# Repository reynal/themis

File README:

Themis is a hybrid analog-digital music synthetizer that leverages both analog and digital hardware to generate the richest synthetizer sound ever.

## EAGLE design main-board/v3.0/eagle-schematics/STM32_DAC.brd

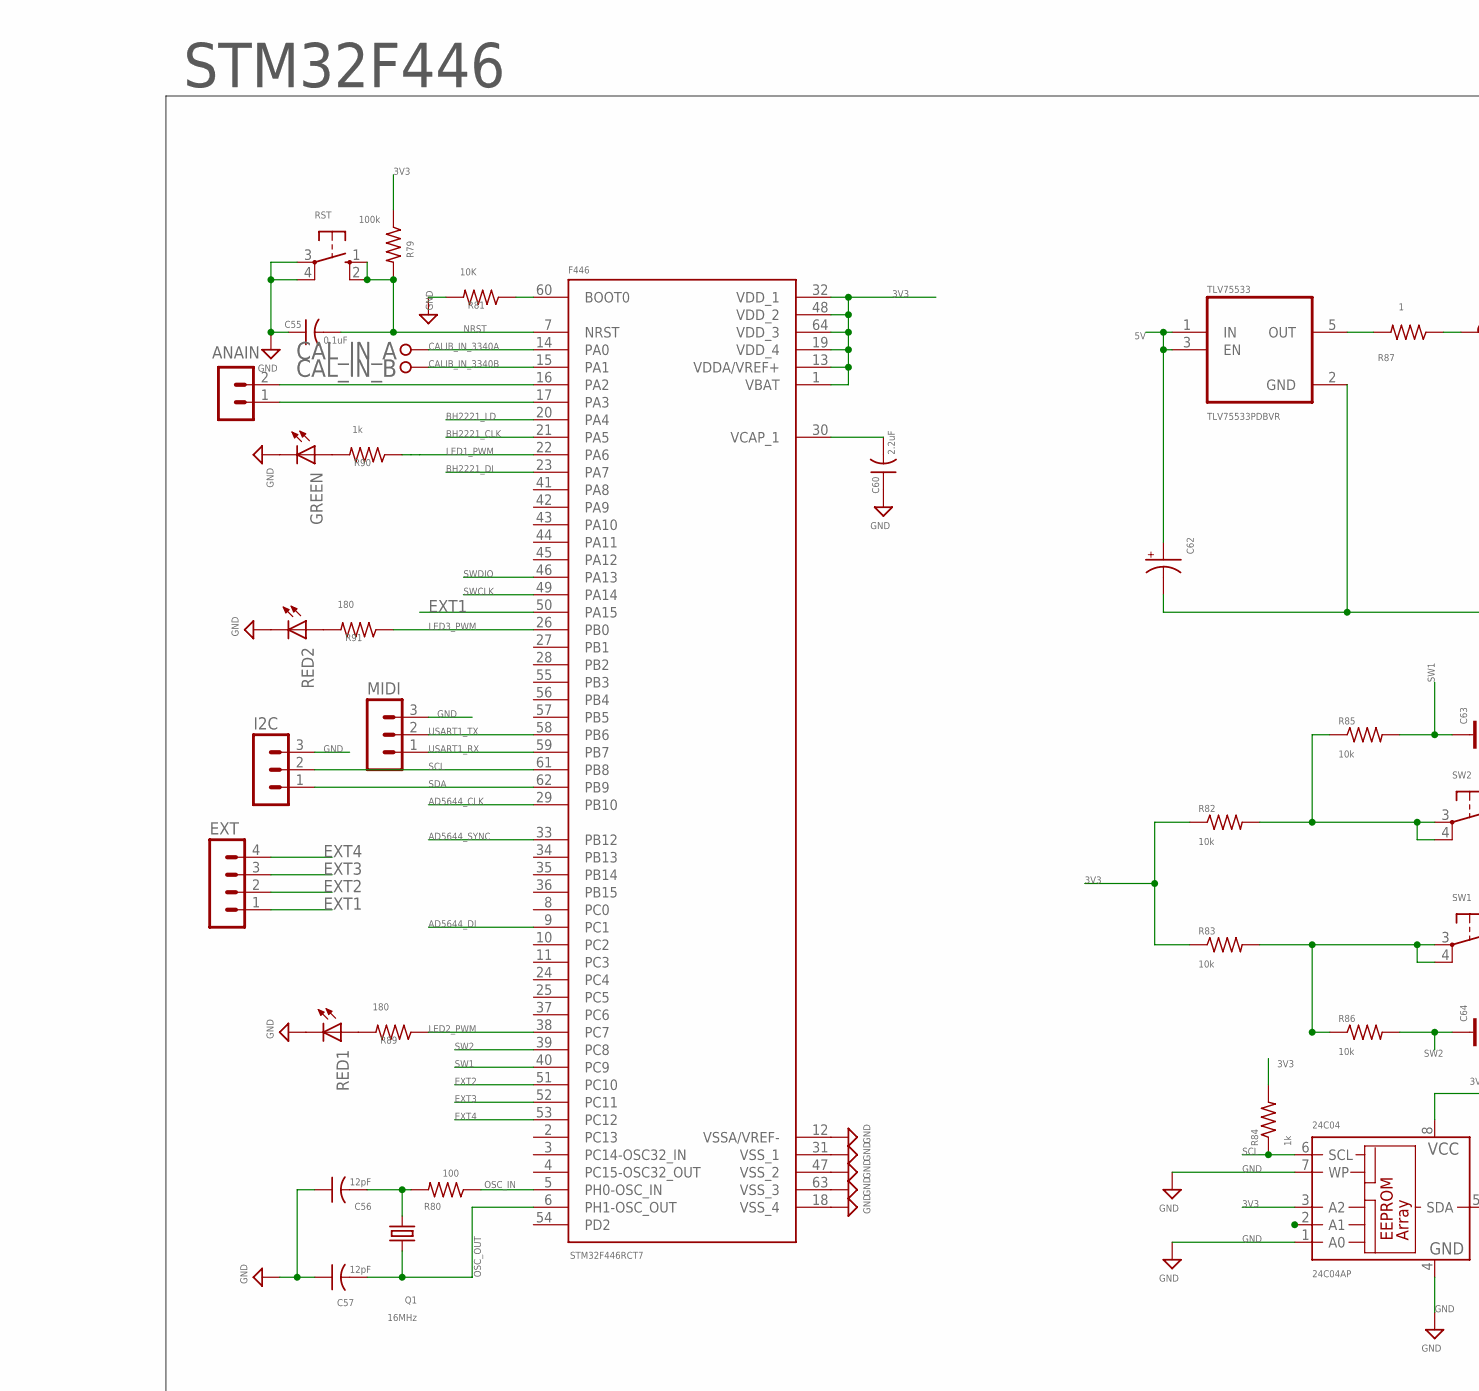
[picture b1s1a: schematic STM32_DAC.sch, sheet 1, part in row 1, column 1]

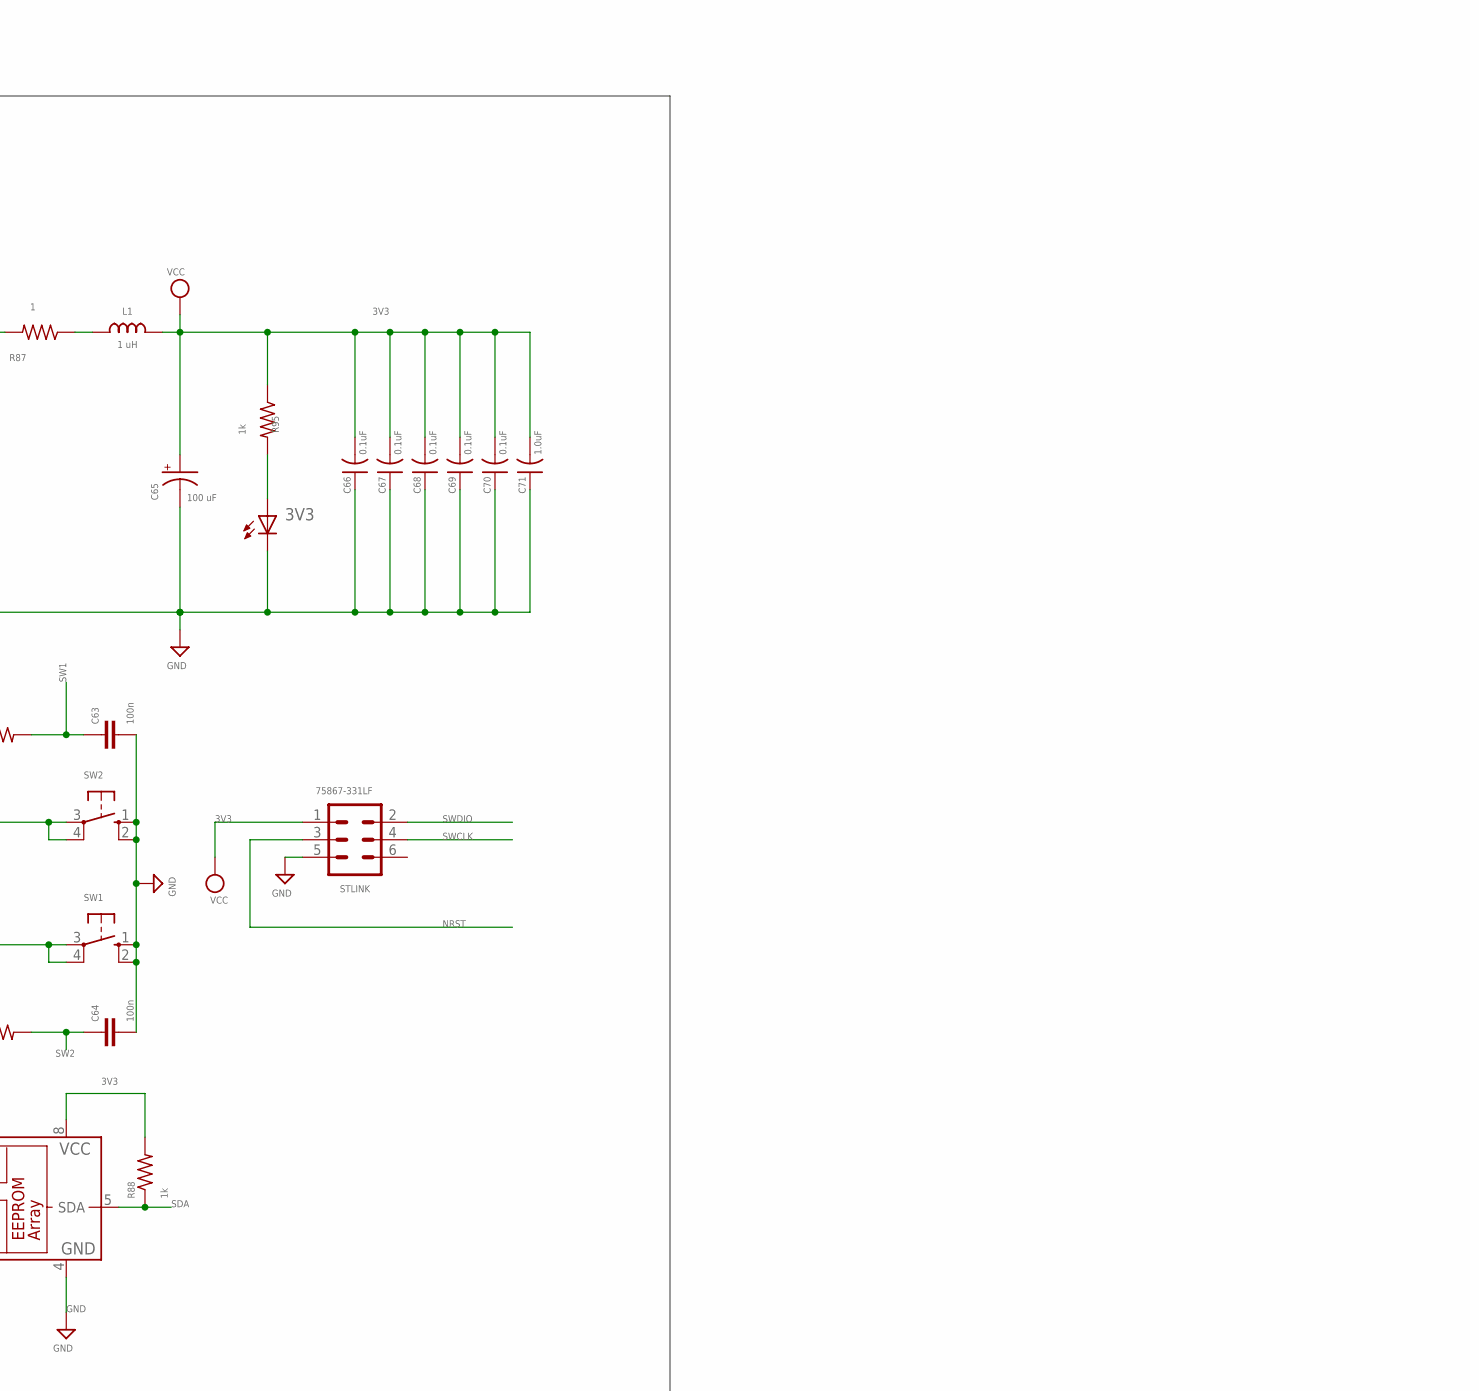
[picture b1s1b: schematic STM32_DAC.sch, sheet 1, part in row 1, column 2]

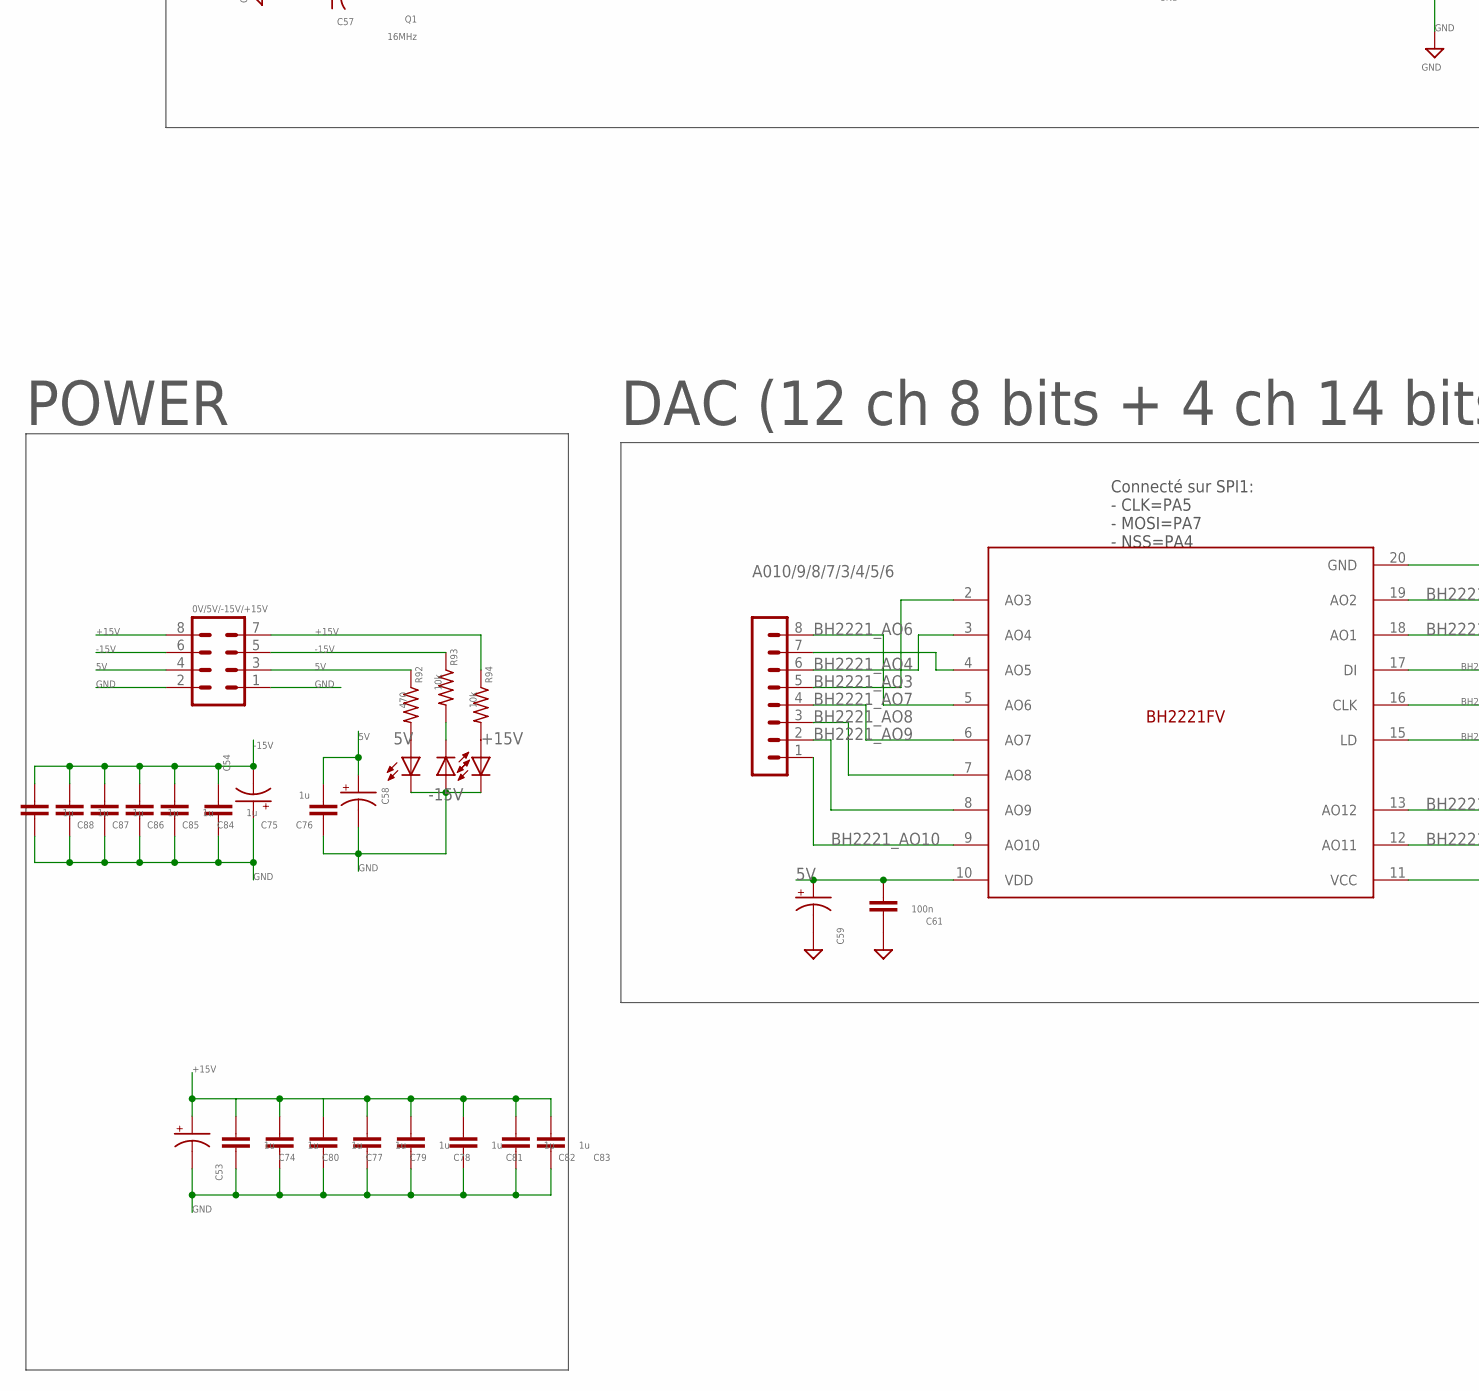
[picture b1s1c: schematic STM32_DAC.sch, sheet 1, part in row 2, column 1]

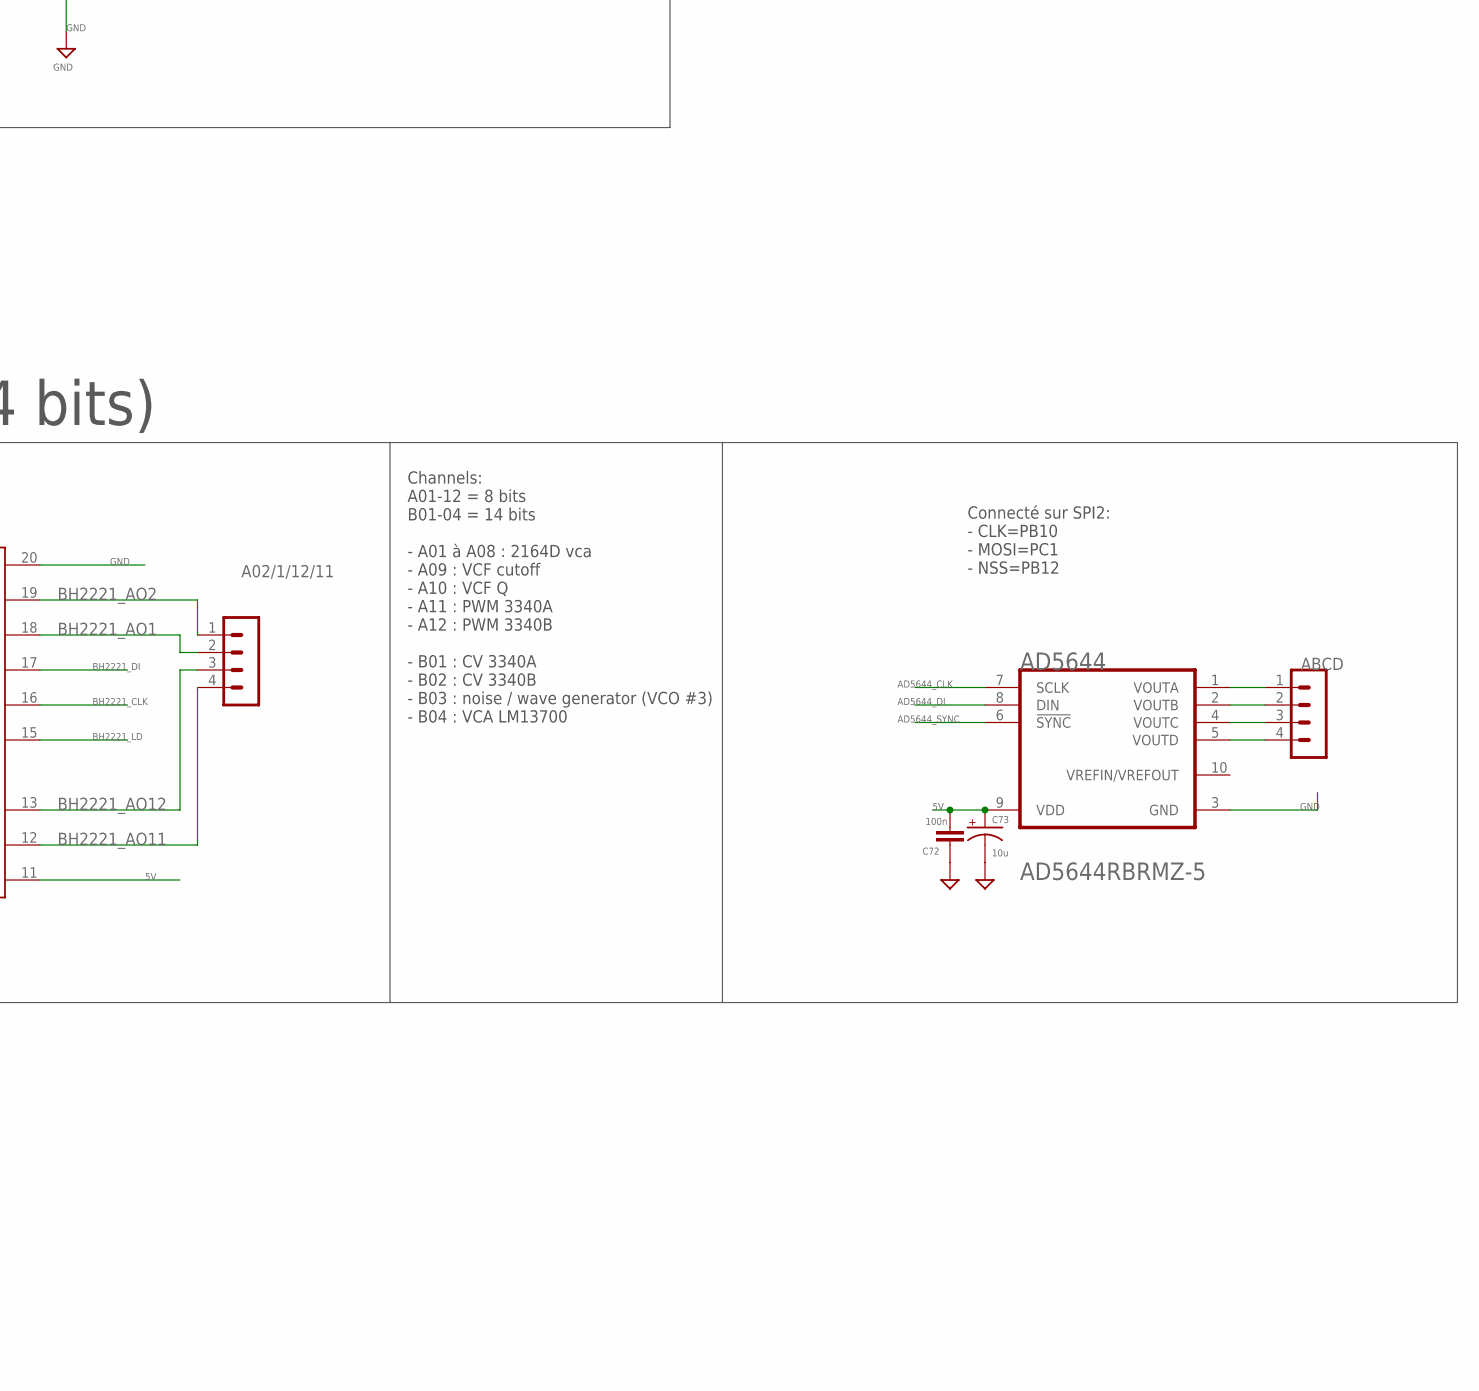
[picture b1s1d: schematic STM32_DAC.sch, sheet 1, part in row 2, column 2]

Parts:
0V/5V/-15V/+15V: MA04-2
3V3: LED-0805; 0805-LED
5V: LED-0603; 0603-LED
24C04: 24C04AP; DIL8
+15V: LED-0805; 0805-LED
-15V: LED-0805; 0805-LED
A02/1/12/11: MA04-1
A010/9/8/7/3/4/5/6: MA08-1
ABCD: MA04-1
AD5644: ANALOG_DEVICES_AD5644RBRMZ-5ANALOG_DEVICES_AD5644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; ANALOG_DEVICES_AD5644RBRMZ-5_0
ANAIN: MA02-1
BH2221: BH2221FV; SOP65P780X200-20N
C53, C54, C58, C59, C62, C73: 10u; CPOL2917
C55, C66, C67, C68, C69, C70: 0.1uF; C0805
C56, C57: 12pF; C0805
C60: 2.2uF; C0805
C61, C72: 100n; C1206
C63, C64: 100n; C0805
C65: 100 uF; CPOL2917
C71: 1.0uF; C0805
C74, C75, C76, C77, C78, C79, C80, C81, C82, C83, C84, C85, C86, C87, C88: 1u; C1206
CAL_IN_A: TESTPOINT; TESTPOINT_63
CAL_IN_B: TESTPOINT; TESTPOINT_63
EXT: MA04-1
F446: STM32F446RCT7; QFP50P1200X1200X160-64N
GREEN: LED-0805; 0805-LED
I2C: MA03-1
L1: 1 uH; L0805
MIDI: MA03-1
Q1: 16MHz; Q-HC-46X
R79: 100k; R0805
R80: 100; R0805
R81: 10K; R0805
R82, R83, R85, R86, R93, R94: 10k; R0805
R84, R88, R90, R95: 1k; R0805
R87: 1; R0805
R89, R91: 180; R0805
R92: 470; R0805
RED1, RED2: LED-0603; 0603-LED
RST: 10-XX; B3F-10XX
STLINK: 75867-331LF; MA03-2
SW1, SW2: 10-XX; B3F-10XX
TLV75533: TLV75533PDBVR; SOT95P280X145-5N

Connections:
3V3: 24C04.2 (A1), 24C04.3 (A2), 24C04.8 (VCC), C65.+, C66.2, C67.2, C68.2, C69.2, C70.2, C71.2, F446.1 (VBAT), F446.13 (VDDA/VREF+), F446.19 (VDD_4), F446.32 (VDD_1), F446.48 (VDD_2), F446.64 (VDD_3), L1.2, R79.1, R82.1, R83.1, R84.2, R88.2, R95.1, STLINK.1
5V: 0V/5V/-15V/+15V.3, 0V/5V/-15V/+15V.4, AD5644.9 (VDD), BH2221.10 (VDD), BH2221.11 (VCC), C58.+, C59.+, C61.2, C62.+, C72.2, C73.+, C76.2, R92.1, TLV75533.1 (IN), TLV75533.3 (EN)
+15V: 0V/5V/-15V/+15V.7, 0V/5V/-15V/+15V.8, C53.+, C74.2, C77.2, C78.2, C79.2, C80.2, C81.2, C82.2, C83.2, R94.1
-15V: 0V/5V/-15V/+15V.5, 0V/5V/-15V/+15V.6, C54.-, C75.2, C84.2, C85.2, C86.2, C87.2, C88.2, R93.1
AD5644_CLK: AD5644.7 (SCLK), F446.29 (PB10)
AD5644_DI: AD5644.8 (DIN), F446.9 (PC1)
AD5644_SYNC: AD5644.6 (!SYNC!), F446.33 (PB12)
BH2221_AO1: A02/1/12/11.2, BH2221.18 (AO1)
BH2221_AO2: A02/1/12/11.1, BH2221.19 (AO2)
BH2221_AO3: A010/9/8/7/3/4/5/6.5, BH2221.2 (AO3)
BH2221_AO4: A010/9/8/7/3/4/5/6.6, BH2221.3 (AO4)
BH2221_AO6: A010/9/8/7/3/4/5/6.8, BH2221.5 (AO6)
BH2221_AO7: A010/9/8/7/3/4/5/6.4, BH2221.6 (AO7)
BH2221_AO8: A010/9/8/7/3/4/5/6.3, BH2221.7 (AO8)
BH2221_AO9: A010/9/8/7/3/4/5/6.2, BH2221.8 (AO9)
BH2221_AO10: A010/9/8/7/3/4/5/6.1, BH2221.9 (AO10)
BH2221_AO11: A02/1/12/11.4, BH2221.12 (AO11)
BH2221_AO12: A02/1/12/11.3, BH2221.13 (AO12)
BH2221_CLK: BH2221.16 (CLK), F446.21 (PA5)
BH2221_DI: BH2221.17 (DI), F446.23 (PA7)
BH2221_LD: BH2221.15 (LD), F446.20 (PA4)
BOOT1: F446.60 (BOOT0), R81.1
CALIB_IN_3340A: CAL_IN_A.P$1, F446.14 (PA0)
CALIB_IN_3340B: CAL_IN_B.P$1, F446.15 (PA1)
EXT1: EXT.1, F446.50 (PA15)
EXT2: EXT.2, F446.51 (PC10)
EXT3: EXT.3, F446.52 (PC11)
EXT4: EXT.4, F446.53 (PC12)
GND: 0V/5V/-15V/+15V.1, 0V/5V/-15V/+15V.2, 3V3.C, 5V.C, 24C04.1 (A0), 24C04.4 (GND), 24C04.7 (WP), +15V.C, -15V.A, AD5644.3 (GND), BH2221.20 (GND), C53.-, C54.+, C55.1, C56.1, C57.1, C58.-, C59.-, C60.1, C61.1, C62.-, C63.2, C64.2, C65.-, C66.1, C67.1, C68.1, C69.1, C70.1, C71.1, C72.1, C73.-, C74.1, C75.1, C76.1, C77.1, C78.1, C79.1, C80.1, C81.1, C82.1, C83.1, C84.1, C85.1, C86.1, C87.1, C88.1, F446.12 (VSSA/VREF-), F446.18 (VSS_4), F446.31 (VSS_1), F446.47 (VSS_2), F446.63 (VSS_3), GREEN.C, I2C.3, MIDI.3, R81.2, RED1.C, RED2.C, RST.3, RST.4 (P1), STLINK.5, SW1.1 (S), SW1.2 (S1), SW2.1 (S), SW2.2 (S1), TLV75533.2 (GND)
LED1_PWM: F446.22 (PA6), R90.1
LED2_PWM: F446.38 (PC7), R89.1
LED3_PWM: F446.26 (PB0), R91.1
unnamed: R82.2, R85.1, SW2.3, SW2.4 (P1)
unnamed: R83.2, R86.1, SW1.3, SW1.4 (P1)
unnamed: A010/9/8/7/3/4/5/6.7, BH2221.4 (AO5)
unnamed: ABCD.1, AD5644.1 (VOUTA)
unnamed: ABCD.2, AD5644.2 (VOUTB)
unnamed: ABCD.3, AD5644.4 (VOUTC)
unnamed: ABCD.4, AD5644.5 (VOUTD)
unnamed: R89.2, RED1.A
unnamed: R91.2, RED2.A
unnamed: 5V.A, R92.2
unnamed: -15V.C, R93.2
unnamed: +15V.A, R94.2
unnamed: GREEN.A, R90.2
unnamed: 3V3.A, R95.2
unnamed: ANAIN.2, F446.16 (PA2)
unnamed: ANAIN.1, F446.17 (PA3)
unnamed: C56.2, Q1.1, R80.2
unnamed: R87.2, TLV75533.5 (OUT)
unnamed: L1.1, R87.1
NRST: C55.2, F446.7 (NRST), R79.2, RST.1 (S), RST.2 (S1), STLINK.3
OSC_IN: F446.5 (PH0-OSC_IN), R80.1
OSC_OUT: C57.2, F446.6 (PH1-OSC_OUT), Q1.2
SCL: 24C04.6 (SCL), F446.61 (PB8), I2C.2, R84.1
SDA: 24C04.5 (SDA), F446.62 (PB9), I2C.1, R88.1
SW1: C63.1, F446.40 (PC9), R85.2
SW2: C64.1, F446.39 (PC8), R86.2
SWCLK: F446.49 (PA14), STLINK.4
SWDIO: F446.46 (PA13), STLINK.2
USART1_RX: F446.59 (PB7), MIDI.1
USART1_TX: F446.58 (PB6), MIDI.2
VCAP1: C60.2, F446.30 (VCAP_1)

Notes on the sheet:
STM32F446
POWER
DAC (12 ch 8 bits + 4 ch 14 bits)
Connecté sur SPI1: - CLK=PA5 - MOSI=PA7 - NSS=PA4
Connecté sur SPI2: - CLK=PB10 - MOSI=PC1 - NSS=PB12
Channels: A01-12 = 8 bits B01-04 = 14 bits - A01 à A08 : 2164D vca - A09 : VCF cutoff - A10 : VCF Q - A11 : PWM 3340A - A12 : PWM 3340B - B01 : CV 3340A - B02 : CV 3340B - B03 : noise / wave generator (VCO #3) - B04 : VCA LM13700

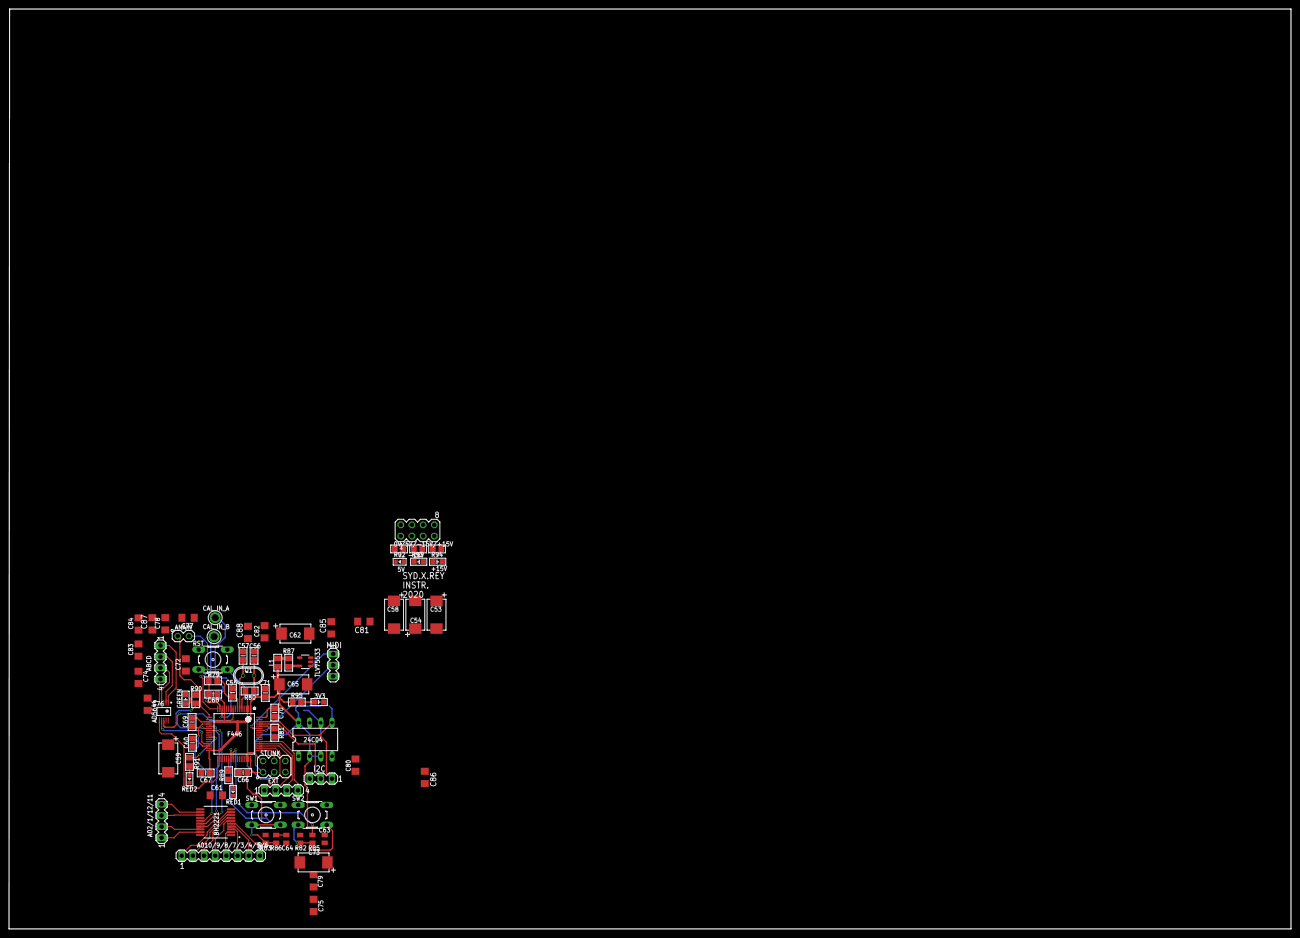
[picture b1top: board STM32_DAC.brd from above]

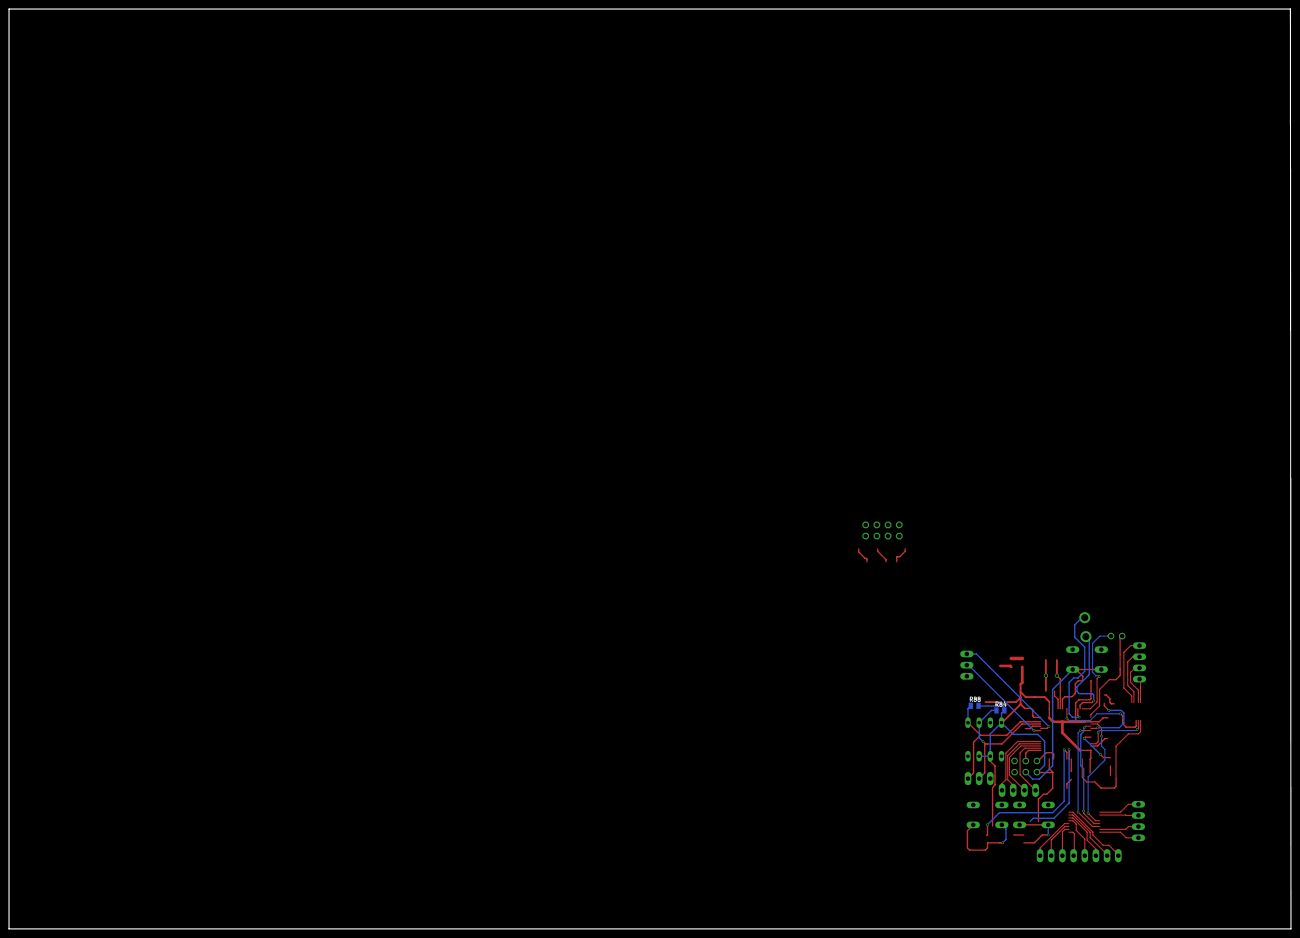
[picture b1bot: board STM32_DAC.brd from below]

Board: 2 copper layers, 291.3 x 209.1 mm, 81 parts (2 on the bottom side), 63 nets.

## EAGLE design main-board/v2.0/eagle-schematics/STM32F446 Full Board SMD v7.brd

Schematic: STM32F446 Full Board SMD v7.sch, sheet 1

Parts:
0V/5V/-15V/+15V: MA04-2
3V3: LED-0805; 0805-LED
5V: LED-0603; 0603-LED
24C04: 24C04AP; DIL8
2164A, 2164B: SSM2164; DIL16
3340A, 3340B: CEM3340; DIL16
+15V: LED-0805; 0805-LED
-15V: LED-0805; 0805-LED
A1, A2, A3, A4: T; TESTPOINT_63
A02/1/12/11: MA04-1
A010/9/8/7/3/4/5/6: MA08-1
ABCD: MA04-1
AD5644: ANALOG_DEVICES_AD5644RBRMZ-5ANALOG_DEVICES_AD5644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; ANALOG_DEVICES_AD5644RBRMZ-5_0
ADG453: ADG453BRZ; SOIC127P600X175-16N
ANAIN: MA02-1
B1, B2, B3, B4: T; TESTPOINT_63
BH2221: BH2221FV; SOP65P780X200-20N
C1, C2, C5, C6, C9, C10, C11, C16, C33, C34, C39, C40, C51, C63, C64: 100n; C0805
C3, C4, C7, C8: 1n; C0805
C12, C13, C14, C15: 10n; C0805
C17, C18, C19, C20, C21, C22, C23, C24, C41: 470n; C0805
C25, C26, C27, C28, C29, C30, C31, C32: 560p; C0805
C35, C46: 100p; C0805
C36, C37, C38: 4.7u; C0805
C42, C44: 1u; C0805
C43, C45, C49, C52: 300p; C0805
C50: 22u; B45181A
C53, C54, C58, C59, C62, C73: 10u; CPOL2917
C55, C66, C67, C68, C69, C70: 0.1uF; C0805
C56, C57: 12pF; C0805
C60: 2.2uF; C0805
C61, C72: 100n; C1206
C65: 100 uF; CPOL2917
C71: 1.0uF; C0805
C74, C75, C76, C77, C78, C79, C80, C81, C82, C83, C84, C85, C86, C87, C88: 1u; C1206
CAL_A: SYNC_IN; TESTPOINT_63
CAL_B: CALIB B; TESTPOINT_63
CAL_IN_A: TESTPOINT; TESTPOINT_63
CAL_IN_B: TESTPOINT; TESTPOINT_63
CUTOFF: TESTPOINT; TESTPOINT_63
CV_A: CV; TESTPOINT_63
CV_B: CV; TESTPOINT_63
CV_TM: 100k; 6MM
EXT: MA04-1
F446: STM32F446RCT7; QFP50P1200X1200X160-64N
FM_B: FMLIN; TESTPOINT_63
GAINS: GAIN_CTRL; MA08-1
GREEN: LED-0805; 0805-LED
HIGH_A: 100k; 6MM
HIGH_B: 100k; 6MM
HOLE1, HOLE2, HOLE3, HOLE4: HOLES_MOUNT-PAD-ROUND-0.096-NS; HOLES_096-PAD-NS
I2C: MA03-1
IN9, IN10: TESTPOINT; TESTPOINT_63
IN34: IN34; MA02-1
ITOV: NE5534AN; DIL08
I_SUM: ITOV; MA08-2
JACK: 1502_01
L1: 1 uH; L0805
LOW_A: 100k; 6MM
LOW_B: 100k; 6MM
MIDI: MA03-1
MIXOUT: TESTPOINT; TESTPOINT_63
MODRING: LM13700M; SO16
Q: TESTPOINT; TESTPOINT_63
Q1: 16MHz; Q-HC-46X
Q_TM: 100k; 6MM
R1, R3: 330k; R0805
R2, R4: 68k; R0805
R5, R6, R51, R52, R63, R82, R83, R85, R86, R93, R94: 10k; R0805
R7, R8: 33k; R0805
R9, R10: 820; R0805
R11, R12: 24k; R0805
R13, R27: 470k; R0805
R14, R15, R16, R17: 5.6k; R0805
R18, R19: 1.8k; R0805
R20, R22, R23, R24, R32, R37, R38, R39, R40, R41, R42, R43, R73, R92: 470; R0805
R21: 1M; R0805
R25, R26: 1.5M; R0805
R28, R29, R30, R31, R33, R34, R35, R36, R46, R47, R58: 27k; R0805
R44, R45: 8.2k; R0805
R48: 33K; R0805
R49, R53, R62, R66, R67, R68, R72, R74, R78, R79: 100k; R0805
R50, R56, R84, R88, R90, R95: 1k; R0805
R54: 1.5k; R0805
R55: 51k; R0805
R57: 4.7k; R0805
R59, R64, R70, R76: 91k; R0805
R60, R69: 47k; R0805
R61: 22k; R0805
R65, R71, R77: 220k; R0805
R75: 100kB; 3RP/1610N
R80: 100; R0805
R81: 10K; R0805
R87: 1; R0805
R89, R91: 180; R0805
RED1, RED2: LED-0603; 0603-LED
RST: 10-XX; B3F-10XX
SAW_A: S; TESTPOINT_63
SAW_B: S; TESTPOINT_63
SD3: SD3; MA02-1
SD4: SD4; MA02-1
SQU_A: P; TESTPOINT_63
SQU_B: P; TESTPOINT_63
STLINK: 75867-331LF; MA03-2
SUB: 4027D; SO16
SUB2, SUB4: T; TESTPOINT_63
SUB_IN: T; TESTPOINT_63
SUM_CON: MA04-2
SUM_OPAMP: NE5534AN; DIL08
SW1, SW2: 10-XX; B3F-10XX
SYNC_A: SYNC_IN; TESTPOINT_63
SYNC_B: SYNC_IN; TESTPOINT_63
TEMCOA: 10k; 6MM
TEMCOB: 10k; 6MM
TLV75533: TLV75533PDBVR; SOT95P280X145-5N
TRI_A: T; TESTPOINT_63
TRI_B: T; TESTPOINT_63
VCA: LM13700M; SO16
VCA_CV: TESTPOINT; TESTPOINT_63
VCA_IN: TESTPOINT; TESTPOINT_63
VCA_OUT: TESTPOINT; TESTPOINT_63
VCF1: AS3320; DIL18
VCF_IN: TESTPOINT; TESTPOINT_63
VCF_OUT: TESTPOINT; TESTPOINT_63
XIN: TESTPOINT; TESTPOINT_63
XMOD: TESTPOINT; TESTPOINT_63

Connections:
3V3: 24C04.2 (A1), 24C04.3 (A2), 24C04.8 (VCC), C65.+, C66.2, C67.2, C68.2, C69.2, C70.2, C71.2, F446.1 (VBAT), F446.13 (VDDA/VREF+), F446.19 (VDD_4), F446.32 (VDD_1), F446.48 (VDD_2), F446.64 (VDD_3), L1.2, R79.1, R82.1, R83.1, R84.2, R88.2, R95.1, STLINK.1
5V: 0V/5V/-15V/+15V.3, 0V/5V/-15V/+15V.4, AD5644.9 (VDD), ADG453.12 (VL), BH2221.10 (VDD), BH2221.11 (VCC), C51.1, C58.+, C59.+, C61.2, C62.+, C72.2, C73.+, C76.2, R92.1, TLV75533.1 (IN), TLV75533.3 (EN)
2164_IN1_MIXA: 2164A.2 (I_IN1), R33.1, R40.1
2164_IN2_MIXA: 2164A.7 (I_IN2), R34.1, R41.1
2164_IN2_MIXB: 2164B.7 (I_IN2), R29.1, R37.1
2164_IN3_MIXA: 2164A.10 (I_IN3), R35.1, R42.1
2164_IN3_MIXB: 2164B.10 (I_IN3), R30.1, R38.1
2164_IN4_MIXA: 2164A.15 (I_IN4), R36.1, R43.1
2164_IN4_MIXB: 2164B.15 (I_IN4), R31.1, R39.1
2164_IN4_MIXB1: 2164B.2 (I_IN1), R28.1, R32.1
2164_MODE_MIXB: 2164B.1 (MODE), R44.2
2164_OUT2_MIXA: 2164A.5 (I_OUT2), I_SUM.4
2164_OUT2_MIXB: 2164B.5 (I_OUT2), I_SUM.14
2164_OUT3_MIXA: 2164A.12 (I_OUT3), I_SUM.8
2164_OUT3_MIXB: 2164B.12 (I_OUT3), I_SUM.16
2164_OUT4_MIXA: 2164A.13 (I_OUT4), I_SUM.6
2164_OUT4_MIXB: 2164B.13 (I_OUT4), I_SUM.12
+15V: 0V/5V/-15V/+15V.7, 0V/5V/-15V/+15V.8, 2164A.16 (V+), 2164B.16 (V+), 3340A.16 (VCC), 3340B.16 (VCC), ADG453.13 (VDD), C5.2, C6.2, C33.2, C39.2, C53.+, C74.2, C77.2, C78.2, C79.2, C80.2, C81.2, C82.2, C83.2, ITOV.7 (V+), LOW_A.E, LOW_B.E, MODRING.11 (V+), R1.2, R3.2, R25.2, R26.2, R44.1, R45.1, R51.1, R60.2, R94.1, SUM_OPAMP.7 (V+), VCA.11 (V+), VCF1.14 (V+)
-15V: 0V/5V/-15V/+15V.5, 0V/5V/-15V/+15V.6, 2164A.9 (V-), 2164B.9 (V-), ADG453.4 (VSS), C34.1, C54.-, C75.2, C84.2, C85.2, C86.2, C87.2, C88.2, ITOV.4 (V-), MODRING.6 (V-), R9.1, R10.1, R54.1, R63.1, R65.1, R71.1, R77.1, R93.1, SUM_OPAMP.4 (V-)
AD5644_A: ABCD.1, AD5644.1 (VOUTA)
AD5644_B: ABCD.2, AD5644.2 (VOUTB)
AD5644_C: ABCD.3, AD5644.4 (VOUTC)
AD5644_CLK: AD5644.7 (SCLK), F446.29 (PB10)
AD5644_D: ABCD.4, AD5644.5 (VOUTD)
AD5644_DI: AD5644.8 (DIN), F446.9 (PC1)
AD5644_SYNC: AD5644.6 (!SYNC!), F446.33 (PB12)
BH2221_AO1: A02/1/12/11.2, BH2221.18 (AO1)
BH2221_AO2: A02/1/12/11.1, BH2221.19 (AO2)
BH2221_AO3: A010/9/8/7/3/4/5/6.5, BH2221.2 (AO3)
BH2221_AO4: A010/9/8/7/3/4/5/6.6, BH2221.3 (AO4)
BH2221_AO5: A010/9/8/7/3/4/5/6.7, BH2221.4 (AO5)
BH2221_AO6: A010/9/8/7/3/4/5/6.8, BH2221.5 (AO6)
BH2221_AO7: A010/9/8/7/3/4/5/6.4, BH2221.6 (AO7)
BH2221_AO8: A010/9/8/7/3/4/5/6.3, BH2221.7 (AO8)
BH2221_AO9: A010/9/8/7/3/4/5/6.2, BH2221.8 (AO9)
BH2221_AO10: A010/9/8/7/3/4/5/6.1, BH2221.9 (AO10)
BH2221_AO11: A02/1/12/11.4, BH2221.12 (AO11)
BH2221_AO12: A02/1/12/11.3, BH2221.13 (AO12)
BH2221_CLK: BH2221.16 (CLK), F446.21 (PA5)
BH2221_DI: BH2221.17 (DI), F446.23 (PA7)
BH2221_LD: BH2221.15 (LD), F446.20 (PA4)
BIAS_VCA: C37.1, R50.2, R51.2, R52.1, SUM_OPAMP.3 (+IN), VCA.4 (IN_N)
BOOT1: F446.60 (BOOT0), R81.1
CALIB_3340A: CAL_A.P$1, R6.1, R8.1
CALIB_3340B: CAL_B.P$1, R5.1, R7.1
CALIB_IN_3340A: CAL_IN_A.P$1, F446.14 (PA0)
CALIB_IN_3340B: CAL_IN_B.P$1, F446.15 (PA1)
CAP1_VCF: C43.2, VCF1.5 (CAP)
CAP2_VCF: C45.2, VCF1.4 (CAP)
CAP3_VCF: C49.2, VCF1.16 (CAP)
CAP4_VCF: C52.2, VCF1.11 (CAP)
CV_CUTOFF: CUTOFF.P$1, CV_TM.E
CV_FREQ_3340A: CV_A.P$1, HIGH_A.E
CV_FREQ_3340B: CV_B.P$1, HIGH_B.E
CV_PWM_3340A: 3340A.5 (PWM_CTRL), R3.1, R4.1
CV_PWM_3340B: 3340B.5 (PWM_CTRL), R1.1, R2.1
CV_RES: Q.P$1, Q_TM.E, Q_TM.S
CV_VCA: R58.1, VCA_CV.P$1
EXT1: EXT.1, F446.50 (PA15)
EXT2: EXT.2, F446.51 (PC10)
EXT3: EXT.3, F446.52 (PC11)
EXT4: EXT.4, F446.53 (PC12)
FEEDBACK_VCF: ADG453.2 (D1), ADG453.15 (D2), C44.1
FMLIN_3340B: C11.2, FM_B.P$1
FREQ_CTRL_3340A: 3340A.15 (FREQ_CTRL), HIGH_A.A, HIGH_A.S, LOW_A.A, LOW_A.S, R24.1
FREQ_CTRL_3340B: 3340B.15 (FREQ_CTRL), HIGH_B.A, HIGH_B.S, LOW_B.A, LOW_B.S, R23.1
FREQ_CV_VCF: CV_TM.S, VCF1.12 (FREQ_CV)
GAIN1_A: 2164A.3 (GAIN_VCA1), GAINS.8
GAIN1_B: 2164B.3 (GAIN_VCA1), GAINS.4
GAIN2_A: 2164A.6 (GAIN_VCA2), GAINS.5
GAIN2_B: 2164B.6 (GAIN_VCA2), GAINS.1
GAIN3_A: 2164A.11 (GAIN_VCA3), GAINS.6
GAIN3_B: 2164B.11 (GAIN_VCA3), GAINS.2
GAIN4_A: 2164A.14 (GAIN_VCA4), GAINS.7
GAIN4_B: 2164B.14 (GAIN_VCA4), GAINS.3
GND: 0V/5V/-15V/+15V.1, 0V/5V/-15V/+15V.2, 3V3.C, 5V.C, 24C04.1 (A0), 24C04.4 (GND), 24C04.7 (WP), 2164A.8 (GND), 2164B.8 (GND), 3340A.12 (GND), 3340B.12 (GND), +15V.C, -15V.A, AD5644.3 (GND), ADG453.5 (GND), BH2221.20 (GND), C1.1, C2.1, C5.1, C6.1, C7.1, C8.1, C9.1, C10.1, C12.1, C13.1, C14.2, C15.2, C16.2, C25.1, C26.1, C27.1, C28.1, C29.1, C30.1, C31.1, C32.1, C33.1, C34.2, C37.2, C39.1, C40.2, C43.1, C45.1, C49.1, C51.2, C52.1, C53.-, C54.+, C55.1, C56.1, C57.1, C58.-, C59.-, C60.1, C61.1, C62.-, C63.2, C64.2, C65.-, C66.1, C67.1, C68.1, C69.1, C70.1, C71.1, C72.1, C73.-, C74.1, C75.1, C76.1, C77.1, C78.1, C79.1, C80.1, C81.1, C82.1, C83.1, C84.1, C85.1, C86.1, C87.1, C88.1, CV_TM.A, F446.12 (VSSA/VREF-), F446.18 (VSS_4), F446.31 (VSS_1), F446.47 (VSS_2), F446.63 (VSS_3), GREEN.C, I2C.3, ITOV.3 (+IN), JACK.1, MIDI.3, MODRING.13 (IN_N), R2.2, R4.2, R5.2, R6.2, R13.1, R18.2, R19.2, R27.1, R52.2, R56.2, R61.1, R66.1, R68.1, R72.2, R75.1 (A), R81.2, RED1.C, RED2.C, RST.3, RST.4 (P1), STLINK.5, SUB.4 (R), SUB.7 (S), SUB.9 (S), SUB.12 (R), SW1.1 (S), SW1.2 (S1), SW2.1 (S), SW2.2 (S1), TLV75533.2 (GND), VCA.6 (V-), VCF1.3 (GND)
HEADIN_OPAMP_OUT: C46.2, R69.2, SUM_CON.1, SUM_CON.2, SUM_CON.3, SUM_CON.4, SUM_CON.5, SUM_CON.6, SUM_CON.7, SUM_CON.8, SUM_OPAMP.2 (-IN)
IN1_MIXERA: A1.P$1, C18.1
IN1_VCF: R59.2, R62.2, VCF1.1 (IN)
IN2_MIXERA: A2.P$1, C20.1
IN2_MIXERB: B2.P$1, C17.1
IN2_VCF: R64.1, R65.2, R67.1, VCF1.2 (IN)
IN3_MIXERA: A3.P$1, C23.1
IN3_MIXERB: B3.P$1, C21.1
IN3_VCF: R70.1, R71.2, R74.1, VCF1.17 (IN)
IN4_MIXERB: B4.P$1, C22.1
IN4_MIXERB1: B1.P$1, C19.1
IN4_VCF: R76.1, R77.2, R78.1, VCF1.18 (IN)
IN_VCF: C41.2, VCF_IN.P$1
IN_VCFORDER: ADG453.1 (IN1), ADG453.16 (IN2), R68.2
IOUT_VCA: VCA.5 (OUT), VCA_OUT.P$1
ITOV_IN: C35.1, ITOV.2 (-IN), I_SUM.1, I_SUM.3, I_SUM.5, I_SUM.7, I_SUM.9, I_SUM.11, I_SUM.13, I_SUM.15, R46.1, R47.1, R48.1
LED1_PWM: F446.22 (PA6), R90.1
LED2_PWM: F446.38 (PC7), R89.1
LED3_PWM: F446.26 (PB0), R91.1
LINEAR_CTRL_3340A: 3340A.13 (LINEAR_CTRL), R22.1, R26.1
LINEAR_CTRL_3340B: 3340B.13 (LINEAR_CTRL), R20.1, R21.1, R25.1
unnamed: 2164B.4 (I_OUT1), I_SUM.10
unnamed: 3340B.6 (HARD_SYNC), C3.2
unnamed: SUB.10 (J), SUB.14 (!Q)
unnamed: 2164A.4 (I_OUT1), I_SUM.2
unnamed: R82.2, R85.1, SW2.3, SW2.4 (P1)
unnamed: A4.P$1, C24.1
unnamed: R83.2, R86.1, SW1.3, SW1.4 (P1)
unnamed: C3.1, R13.2, SYNC_B.P$1
unnamed: ADG453.6 (S4), SD4.2
unnamed: C25.2, R32.2
unnamed: C19.2, R28.2
unnamed: MODRING.14 (IN_P), R53.2, R56.1
unnamed: C36.2, R49.2
unnamed: IN9.P$1, R46.2
unnamed: IN10.P$1, R47.2
unnamed: ADG453.7 (D4), SD4.1
unnamed: R58.2, VCA.1 (I_BIAS)
unnamed: ADG453.11 (S3), SD3.1
unnamed: C26.2, R37.2
unnamed: C27.2, R38.2
unnamed: C28.2, R39.2
unnamed: ADG453.10 (D3), SD3.2
unnamed: ADG453.9 (IN3), IN34.1, R72.1
unnamed: 2164A.1 (MODE), R45.2
unnamed: SUB.2 (!Q), SUB.6 (J)
unnamed: C16.1, SUB.5 (K), SUB.11 (K), SUB.16 (VDD)
unnamed: C38.1, R53.1
unnamed: MODRING.9 (E), R63.2
unnamed: C42.1, MODRING.16 (I_BIAS), R60.1
unnamed: C42.2, R57.1
unnamed: C36.1, R50.1, VCA.3 (IN_P)
unnamed: R89.2, RED1.A
unnamed: R57.2, XMOD.P$1
unnamed: C38.2, XIN.P$1
unnamed: MODRING.10 (B), MODRING.12 (OUT), R61.2
unnamed: R91.2, RED2.A
unnamed: 5V.A, R92.2
unnamed: -15V.C, R93.2
unnamed: +15V.A, R94.2
unnamed: GREEN.A, R90.2
unnamed: 3V3.A, R95.2
unnamed: ANAIN.2, F446.16 (PA2)
unnamed: ANAIN.1, F446.17 (PA3)
unnamed: C21.2, R30.2
unnamed: C17.2, R29.2
unnamed: C22.2, R31.2
unnamed: C30.2, R41.2
unnamed: C29.2, R40.2
unnamed: C31.2, R42.2
unnamed: C32.2, R43.2
unnamed: C18.2, R33.2
unnamed: C23.2, R35.2
unnamed: C20.2, R34.2
unnamed: C24.2, R36.2
unnamed: C56.2, Q1.1, R80.2
unnamed: R87.2, TLV75533.5 (OUT)
unnamed: L1.1, R87.1
unnamed: C41.1, R59.1
unnamed: C12.2, R23.2
unnamed: C14.1, R20.2
unnamed: 3340B.1 (MUL_GAIN1), TEMCOB.A
unnamed: R11.1, TEMCOB.E, TEMCOB.S
unnamed: C11.1, R21.2
unnamed: 3340B.8 (SAW_OUT), R14.2
unnamed: C13.2, R24.2
unnamed: C15.1, R22.2
unnamed: 3340A.1 (MUL_GAIN1), TEMCOA.A
unnamed: R12.1, TEMCOA.E, TEMCOA.S
unnamed: 3340A.8 (SAW_OUT), R15.2
unnamed: 3340A.6 (HARD_SYNC), C4.2
NRST: C55.2, F446.7 (NRST), R79.2, RST.1 (S), RST.2 (S1), STLINK.3
OSC_IN: F446.5 (PH0-OSC_IN), R80.1
OSC_OUT: C57.2, F446.6 (PH1-OSC_OUT), Q1.2
OUT1_VCF: R62.1, R64.2, VCF1.7 (OUT)
OUT2_VCF: ADG453.3 (S1), R67.2, R70.2, VCF1.6 (OUT)
OUT3_VCF: R74.2, R76.2, VCF1.15 (OUT)
OUT4_VCF: ADG453.14 (S2), R78.2, VCF1.10 (OUT)
OUT_JACK: C50.-, JACK.2 (3), JACK.3 (2)
OUT_MIXER: C35.2, ITOV.6 (OUT), MIXOUT.P$1, R48.2
OUT_OPAMP: C46.1, R69.1, R73.2, SUM_OPAMP.6 (OUT)
OUT_POT: C50.+, R73.1, R75.2 (S), R75.3 (E)
OUT_VCF: C44.2, R55.2, VCF_OUT.P$1
PULSE_3340A: 3340A.4 (PULSE_OUT), R8.2, SQU_A.P$1
PULSE_3340B: 3340B.4 (PULSE_OUT), R7.2, SQU_B.P$1
RES_CUR_IN_VCF: R55.1, VCF1.8 (IN_RES)
RES_CUR_VCF: Q_TM.A, VCF1.9 (RES_CUR)
SAW_3340A: R15.1, SAW_A.P$1
SAW_3340B: R14.1, SAW_B.P$1
SCALE_3340A: 3340A.14 (SCALE), R19.1
SCALE_3340B: 3340B.14 (SCALE), R18.1
SCL: 24C04.6 (SCL), F446.61 (PB8), I2C.2, R84.1
SDA: 24C04.5 (SDA), F446.62 (PB9), I2C.1, R88.1
SOFT_SYNC_3340A: 3340A.9 (SOFT_SYNC), C10.2
SOFT_SYNC_3340B: 3340B.9 (SOFT_SYNC), C9.2
SUB_IN: SUB.3 (CLK), SUB_IN.P$1
SUB_OUT2: SUB.1 (Q), SUB.13 (CLK), SUB2.P$1
SUB_OUT4: SUB.15 (Q), SUB4.P$1
SW1: C63.1, F446.40 (PC9), R85.2
SW2: C64.1, F446.39 (PC8), R86.2
SWCLK: F446.49 (PA14), STLINK.4
SWDIO: F446.46 (PA13), STLINK.2
SYNC_3340A: C4.1, R27.2, SYNC_A.P$1
TEMPCO2_VCOA: 3340A.2 (MUL_GAIN2), R17.1
TEMPCO2_VCOB: 3340B.2 (MUL_GAIN2), R16.1
TIMING_CAP_3340A: 3340A.11 (TIMING_CAP), C8.2
TIMING_CAP_3340B: 3340B.11 (TIMING_CAP), C7.2
TRI_3340A: 3340A.10 (TRI_OUT), TRI_A.P$1
TRI_3340B: 3340B.10 (TRI_OUT), TRI_B.P$1
USART1_RX: F446.59 (PB7), MIDI.1
USART1_TX: F446.58 (PB6), MIDI.2
VCAP1: C60.2, F446.30 (VCAP_1)
VCA_IN: R49.1, VCA_IN.P$1
VCF_ANASW_IN4: ADG453.8 (IN4), IN34.2, R66.2
VEE_VCF: C40.1, R54.2, VCF1.13 (V-)
VEE_VCOA: 3340A.3 (VEE), C2.2, R10.2, R12.2, R17.2
VEE_VCOB: 3340B.3 (VEE), C1.2, R9.2, R11.2, R16.2
VSS: SUB.8 (VSS)

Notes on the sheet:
Mixers A and B, 4 channels each (w/o VCA channel)
current -> voltage converter
According to the AS3320 datasheet, control voltage at pin 12 ranges from 0 to 200mV.
AS3320 VCF
Low Pass 2nd Order
Low Pass 4th Order
VCA
Connect 2 and 3 to bypass VCF. Otherwise connect 1 with 2, and 3 with 4.
STM32F446
Note: for a polyphonic synth, voice summing is performed here on the inverting input of the op amp.
Output summing stage
Protection againt short circuits
POWER
DAC (12 ch 8 bits + 4 ch 14 bits)
Connecté sur SPI1: - CLK=PA5 - MOSI=PA7 - NSS=PA4
Connecté sur SPI2: - CLK=PB10 - MOSI=PC1 - NSS=PB12
Channels: A01-12 = 8 bits B01-04 = 14 bits - A01 à A08 : 2164D vca - A09 : VCF cutoff - A10 : VCF Q - A11 : PWM 3340A - A12 : PWM 3340B - B01 : CV 3340A - B02 : CV 3340B - B03 : noise / wave generator (VCO #3) - B04 : VCA LM13700
VCO3340B
VCO3340A
MOD RING

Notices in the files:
front-pane/eagle-schematics/v3/STM32F446 front pane - south - v3.brd:
(c) 2021
front-pane/eagle-schematics/v3/STM32F446 front pane - v3.brd:
RAINBOW by SYD X. REY (c) 2021
